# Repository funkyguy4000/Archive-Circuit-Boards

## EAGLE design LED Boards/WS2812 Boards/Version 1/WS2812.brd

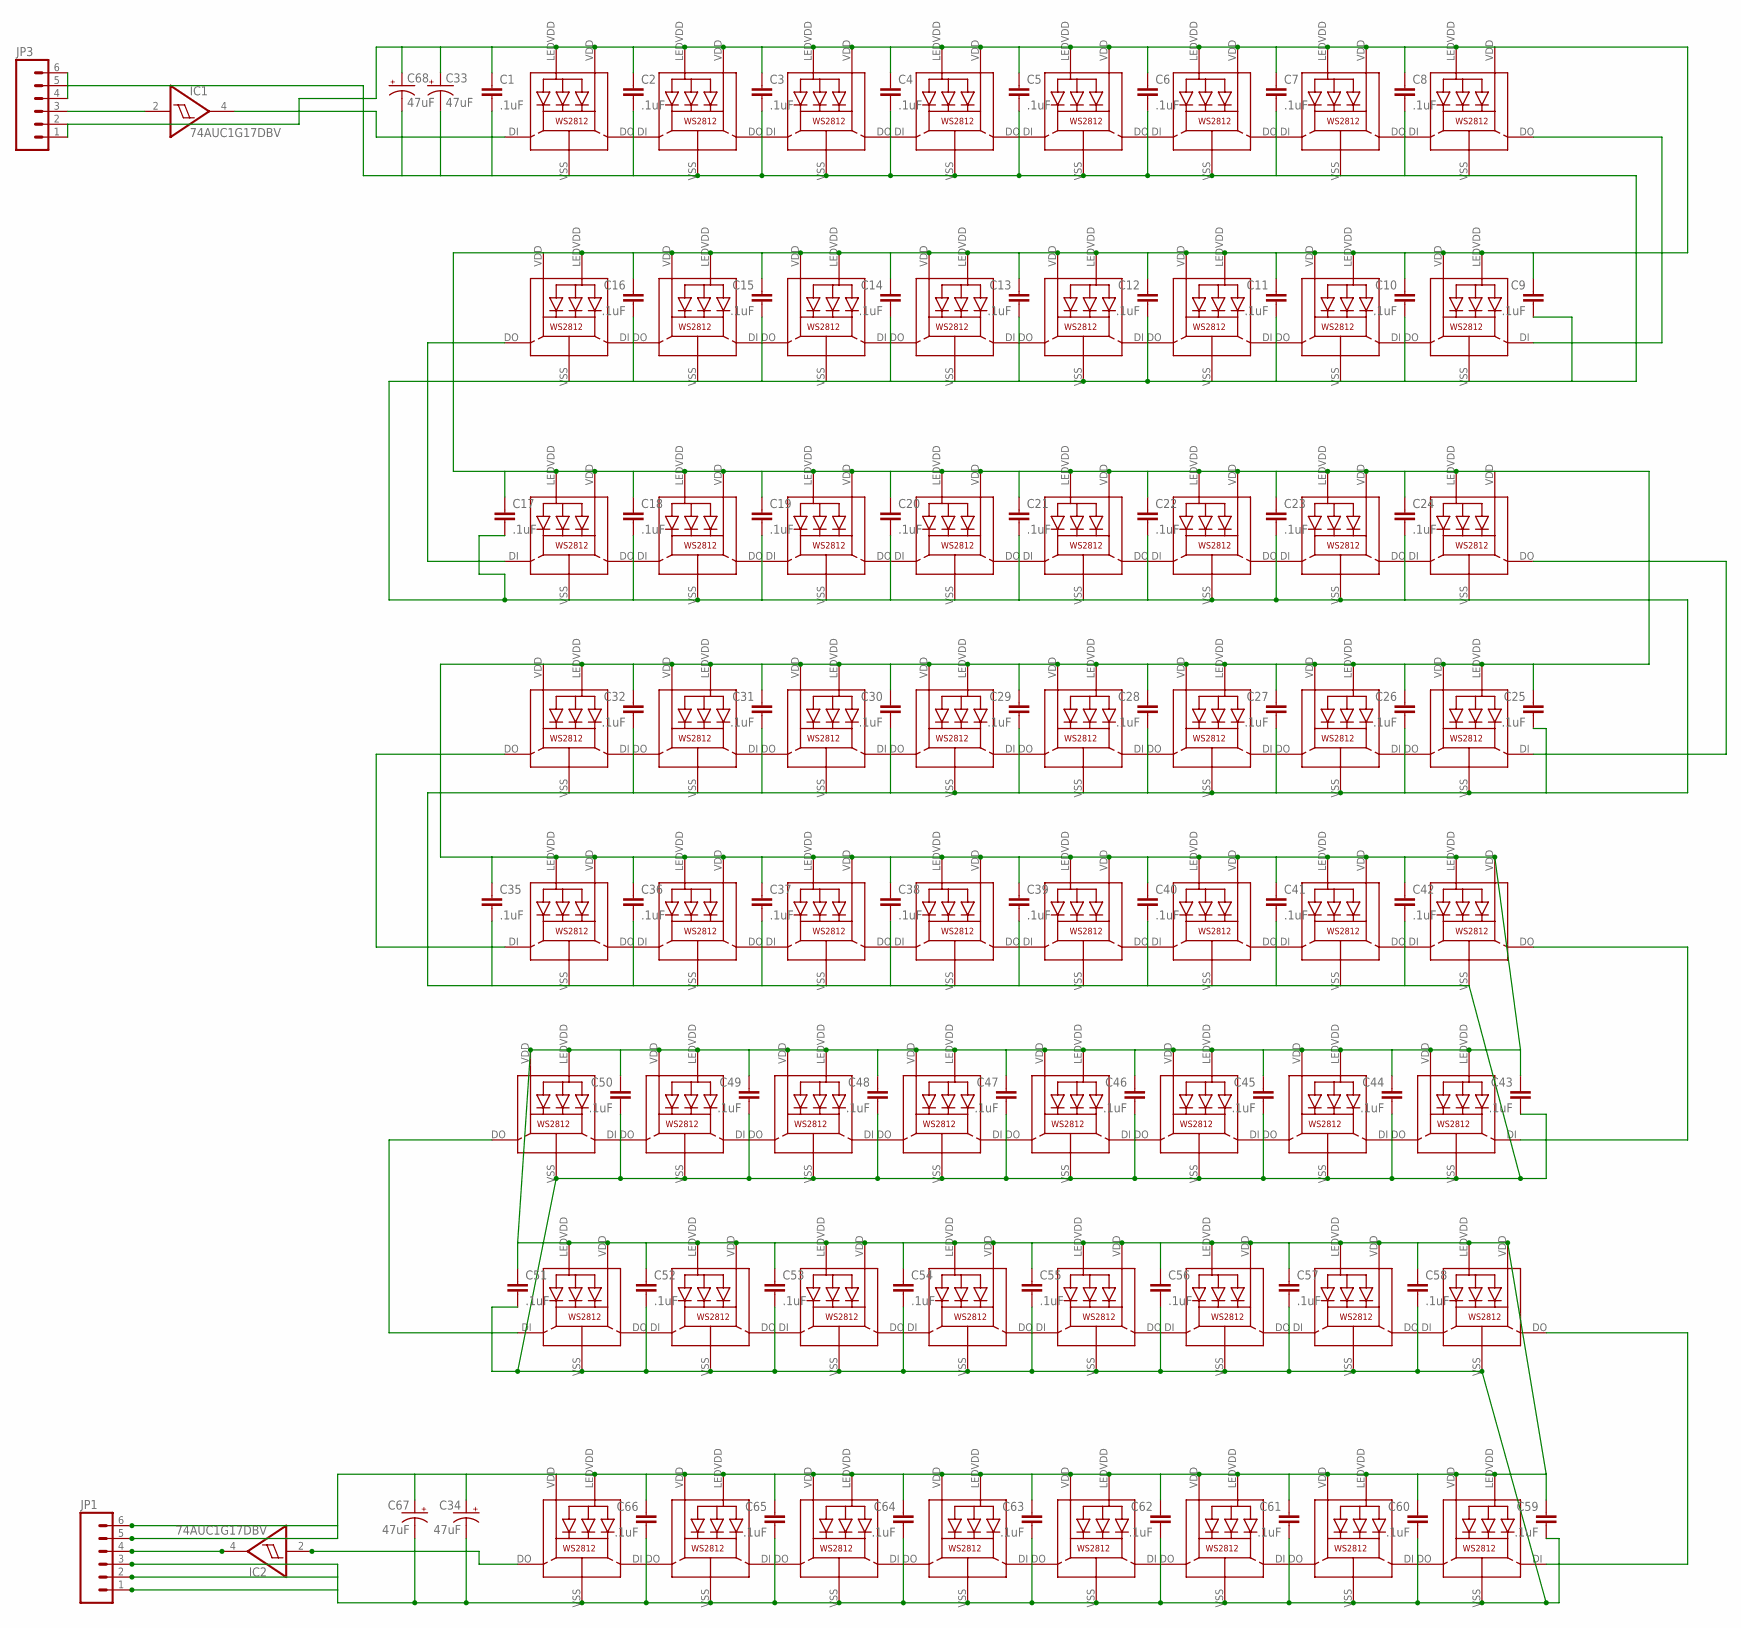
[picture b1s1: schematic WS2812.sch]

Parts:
C1, C2, C3, C4, C5, C6, C7, C8, C9, C10, C11, C12, C13, C14, C15, C16, C17, C18, C19, C20, C21, C22, C23, C24, C25, C26, C27, C28, C29, C30, C31, C32, C35, C36, C37, C38, C39, C40, C41, C42, C43, C44, C45, C46, C47, C48, C49, C50, C51, C52, C53, C54, C55, C56, C57, C58, C59, C60, C61, C62, C63, C64, C65, C66: .1uF; 0603-CAP
C33, C34, C67, C68: 47uF; EIA3216
IC1, IC2: 74AUC1G17DBV; SOT23-5
JP1, JP3: M06SMD; 1X06-SMD
LED1, LED2, LED3, LED4, LED5, LED6, LED7, LED8, LED9, LED10, LED11, LED12, LED13, LED14, LED15, LED16, LED17, LED18, LED19, LED20, LED21, LED22, LED23, LED24, LED25, LED26, LED27, LED28, LED29, LED30, LED31, LED32, LED33, LED34, LED35, LED36, LED37, LED38, LED39, LED40, LED41, LED42, LED43, LED44, LED45, LED46, LED47, LED48, LED49, LED50, LED51, LED52, LED53, LED54, LED55, LED56, LED57, LED58, LED59, LED60, LED61, LED62, LED63, LED64: WS2812

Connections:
DIN: IC1.4 (O), LED1.DI
DIN1: LED32.DO, LED33.DI
DIN_B: IC1.2 (I), JP3.3
DO: IC2.4 (O), JP1.4
DO_B: IC2.2 (I), LED64.DO
GND: C1.2, C2.2, C3.2, C4.2, C5.2, C6.2, C7.2, C8.2, C9.2, C10.2, C11.2, C12.2, C13.2, C14.2, C15.2, C16.2, C17.2, C18.2, C19.2, C20.2, C21.2, C22.2, C23.2, C24.2, C25.2, C26.2, C27.2, C28.2, C29.2, C30.2, C31.2, C32.2, C33.C (-), C34.C (-), C35.2, C36.2, C37.2, C38.2, C39.2, C40.2, C41.2, C42.2, C43.2, C44.2, C45.2, C46.2, C47.2, C48.2, C49.2, C50.2, C51.2, C52.2, C53.2, C54.2, C55.2, C56.2, C57.2, C58.2, C59.2, C60.2, C61.2, C62.2, C63.2, C64.2, C65.2, C66.2, C67.C (-), C68.C (-), IC1.3 (GND), IC2.3 (GND), JP1.1, JP1.2, JP1.3, JP3.4, JP3.5, JP3.6, LED1.VSS (GND), LED2.VSS (GND), LED3.VSS (GND), LED4.VSS (GND), LED5.VSS (GND), LED6.VSS (GND), LED7.VSS (GND), LED8.VSS (GND), LED9.VSS (GND), LED10.VSS (GND), LED11.VSS (GND), LED12.VSS (GND), LED13.VSS (GND), LED14.VSS (GND), LED15.VSS (GND), LED16.VSS (GND), LED17.VSS (GND), LED18.VSS (GND), LED19.VSS (GND), LED20.VSS (GND), LED21.VSS (GND), LED22.VSS (GND), LED23.VSS (GND), LED24.VSS (GND), LED25.VSS (GND), LED26.VSS (GND), LED27.VSS (GND), LED28.VSS (GND), LED29.VSS (GND), LED30.VSS (GND), LED31.VSS (GND), LED32.VSS (GND), LED33.VSS (GND), LED34.VSS (GND), LED35.VSS (GND), LED36.VSS (GND), LED37.VSS (GND), LED38.VSS (GND), LED39.VSS (GND), LED40.VSS (GND), LED41.VSS (GND), LED42.VSS (GND), LED43.VSS (GND), LED44.VSS (GND), LED45.VSS (GND), LED46.VSS (GND), LED47.VSS (GND), LED48.VSS (GND), LED49.VSS (GND), LED50.VSS (GND), LED51.VSS (GND), LED52.VSS (GND), LED53.VSS (GND), LED54.VSS (GND), LED55.VSS (GND), LED56.VSS (GND), LED57.VSS (GND), LED58.VSS (GND), LED59.VSS (GND), LED60.VSS (GND), LED61.VSS (GND), LED62.VSS (GND), LED63.VSS (GND), LED64.VSS (GND)
unnamed: LED1.DO, LED2.DI
unnamed: LED2.DO, LED3.DI
unnamed: LED3.DO, LED4.DI
unnamed: LED5.DO, LED6.DI
unnamed: LED6.DO, LED7.DI
unnamed: LED7.DO, LED8.DI
unnamed: LED9.DO, LED10.DI
unnamed: LED10.DO, LED11.DI
unnamed: LED11.DO, LED12.DI
unnamed: LED13.DO, LED14.DI
unnamed: LED14.DO, LED15.DI
unnamed: LED15.DO, LED16.DI
unnamed: LED17.DO, LED18.DI
unnamed: LED18.DO, LED19.DI
unnamed: LED19.DO, LED20.DI
unnamed: LED21.DO, LED22.DI
unnamed: LED22.DO, LED23.DI
unnamed: LED23.DO, LED24.DI
unnamed: LED25.DO, LED26.DI
unnamed: LED26.DO, LED27.DI
unnamed: LED27.DO, LED28.DI
unnamed: LED29.DO, LED30.DI
unnamed: LED30.DO, LED31.DI
unnamed: LED31.DO, LED32.DI
unnamed: LED4.DO, LED5.DI
unnamed: LED16.DO, LED17.DI
unnamed: LED33.DO, LED34.DI
unnamed: LED34.DO, LED35.DI
unnamed: LED35.DO, LED36.DI
unnamed: LED37.DO, LED38.DI
unnamed: LED38.DO, LED39.DI
unnamed: LED39.DO, LED40.DI
unnamed: LED41.DO, LED42.DI
unnamed: LED42.DO, LED43.DI
unnamed: LED43.DO, LED44.DI
unnamed: LED45.DO, LED46.DI
unnamed: LED46.DO, LED47.DI
unnamed: LED47.DO, LED48.DI
unnamed: LED49.DO, LED50.DI
unnamed: LED50.DO, LED51.DI
unnamed: LED51.DO, LED52.DI
unnamed: LED53.DO, LED54.DI
unnamed: LED54.DO, LED55.DI
unnamed: LED55.DO, LED56.DI
unnamed: LED57.DO, LED58.DI
unnamed: LED58.DO, LED59.DI
unnamed: LED59.DO, LED60.DI
unnamed: LED61.DO, LED62.DI
unnamed: LED62.DO, LED63.DI
unnamed: LED63.DO, LED64.DI
unnamed: LED12.DO, LED13.DI
unnamed: LED20.DO, LED21.DI
unnamed: LED44.DO, LED45.DI
unnamed: LED52.DO, LED53.DI
unnamed: LED28.DO, LED29.DI
unnamed: LED8.DO, LED9.DI
unnamed: LED40.DO, LED41.DI
unnamed: LED24.DO, LED25.DI
unnamed: LED36.DO, LED37.DI
unnamed: LED60.DO, LED61.DI
unnamed: LED48.DO, LED49.DI
unnamed: LED56.DO, LED57.DI
VDD: C1.1, C2.1, C3.1, C4.1, C5.1, C6.1, C7.1, C8.1, C9.1, C10.1, C11.1, C12.1, C13.1, C14.1, C15.1, C16.1, C17.1, C18.1, C19.1, C20.1, C21.1, C22.1, C23.1, C24.1, C25.1, C26.1, C27.1, C28.1, C29.1, C30.1, C31.1, C32.1, C33.A (+), C34.A (+), C35.1, C36.1, C37.1, C38.1, C39.1, C40.1, C41.1, C42.1, C43.1, C44.1, C45.1, C46.1, C47.1, C48.1, C49.1, C50.1, C51.1, C52.1, C53.1, C54.1, C55.1, C56.1, C57.1, C58.1, C59.1, C60.1, C61.1, C62.1, C63.1, C64.1, C65.1, C66.1, C67.A (+), C68.A (+), IC1.5 (VCC), IC2.5 (VCC), JP1.5, JP1.6, JP3.1, JP3.2, LED1.LEDVDD, LED1.VDD, LED2.LEDVDD, LED2.VDD, LED3.LEDVDD, LED3.VDD, LED4.LEDVDD, LED4.VDD, LED5.LEDVDD, LED5.VDD, LED6.LEDVDD, LED6.VDD, LED7.LEDVDD, LED7.VDD, LED8.LEDVDD, LED8.VDD, LED9.LEDVDD, LED9.VDD, LED10.LEDVDD, LED10.VDD, LED11.LEDVDD, LED11.VDD, LED12.LEDVDD, LED12.VDD, LED13.LEDVDD, LED13.VDD, LED14.LEDVDD, LED14.VDD, LED15.LEDVDD, LED15.VDD, LED16.LEDVDD, LED16.VDD, LED17.LEDVDD, LED17.VDD, LED18.LEDVDD, LED18.VDD, LED19.LEDVDD, LED19.VDD, LED20.LEDVDD, LED20.VDD, LED21.LEDVDD, LED21.VDD, LED22.LEDVDD, LED22.VDD, LED23.LEDVDD, LED23.VDD, LED24.LEDVDD, LED24.VDD, LED25.LEDVDD, LED25.VDD, LED26.LEDVDD, LED26.VDD, LED27.LEDVDD, LED27.VDD, LED28.LEDVDD, LED28.VDD, LED29.LEDVDD, LED29.VDD, LED30.LEDVDD, LED30.VDD, LED31.LEDVDD, LED31.VDD, LED32.LEDVDD, LED32.VDD, LED33.LEDVDD, LED33.VDD, LED34.LEDVDD, LED34.VDD, LED35.LEDVDD, LED35.VDD, LED36.LEDVDD, LED36.VDD, LED37.LEDVDD, LED37.VDD, LED38.LEDVDD, LED38.VDD, LED39.LEDVDD, LED39.VDD, LED40.LEDVDD, LED40.VDD, LED41.LEDVDD, LED41.VDD, LED42.LEDVDD, LED42.VDD, LED43.LEDVDD, LED43.VDD, LED44.LEDVDD, LED44.VDD, LED45.LEDVDD, LED45.VDD, LED46.LEDVDD, LED46.VDD, LED47.LEDVDD, LED47.VDD, LED48.LEDVDD, LED48.VDD, LED49.LEDVDD, LED49.VDD, LED50.LEDVDD, LED50.VDD, LED51.LEDVDD, LED51.VDD, LED52.LEDVDD, LED52.VDD, LED53.LEDVDD, LED53.VDD, LED54.LEDVDD, LED54.VDD, LED55.LEDVDD, LED55.VDD, LED56.LEDVDD, LED56.VDD, LED57.LEDVDD, LED57.VDD, LED58.LEDVDD, LED58.VDD, LED59.LEDVDD, LED59.VDD, LED60.LEDVDD, LED60.VDD, LED61.LEDVDD, LED61.VDD, LED62.LEDVDD, LED62.VDD, LED63.LEDVDD, LED63.VDD, LED64.LEDVDD, LED64.VDD

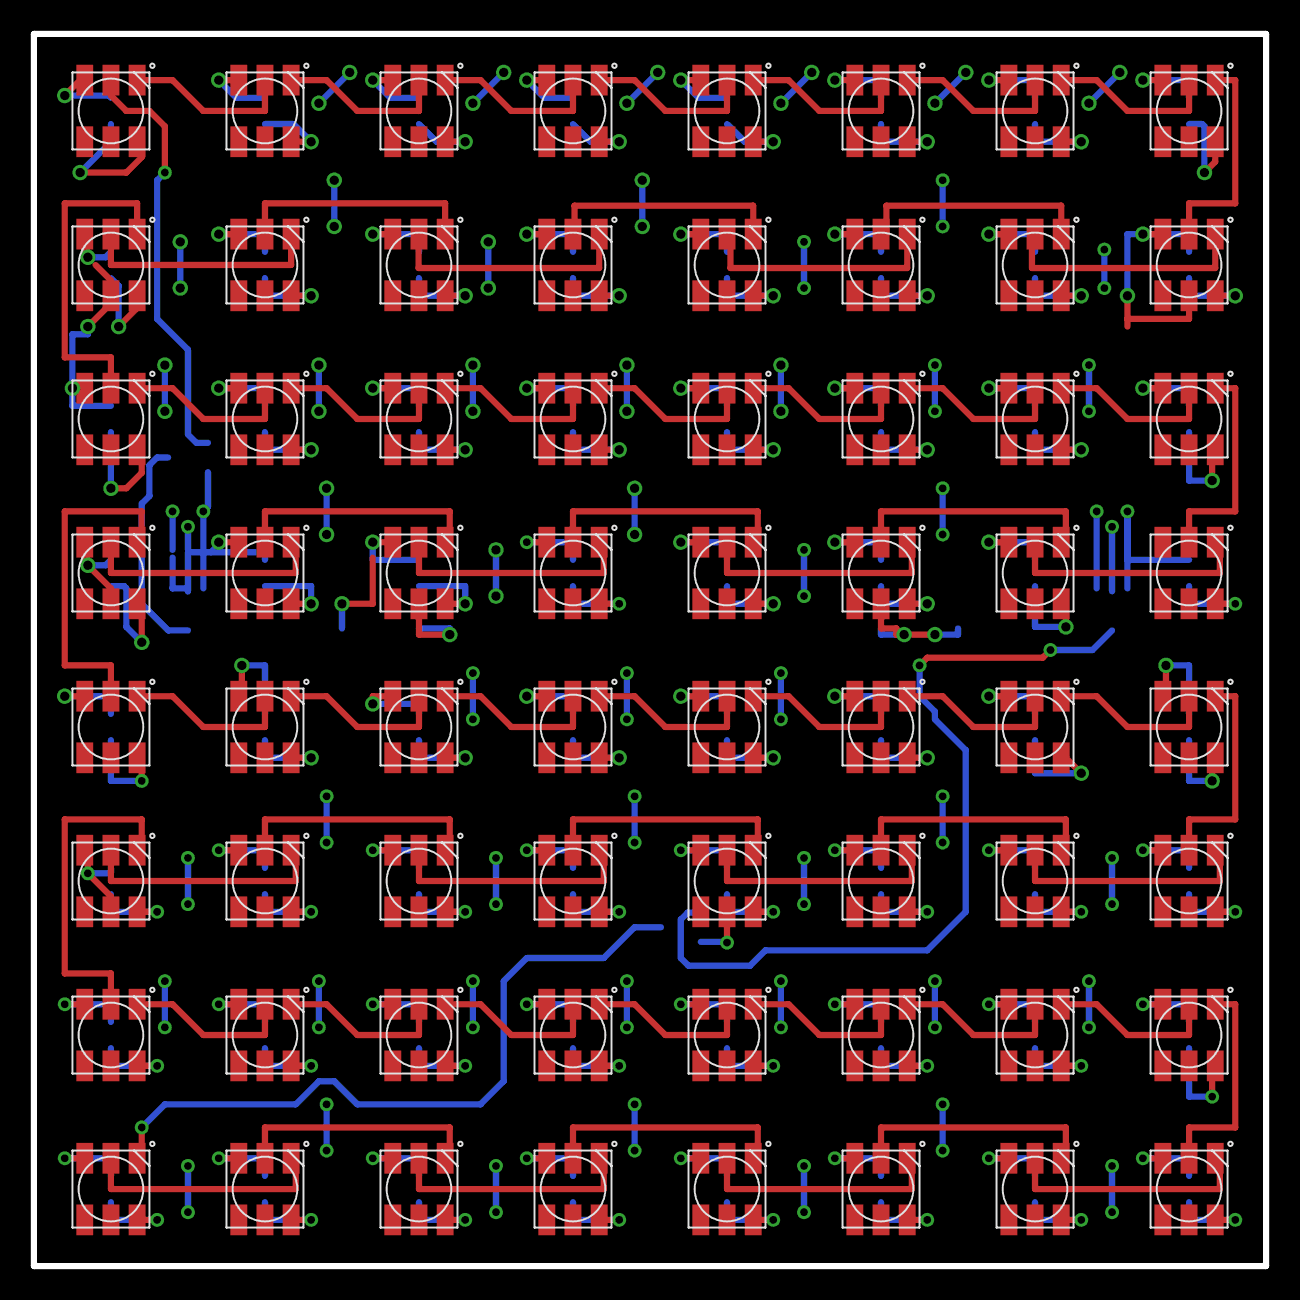
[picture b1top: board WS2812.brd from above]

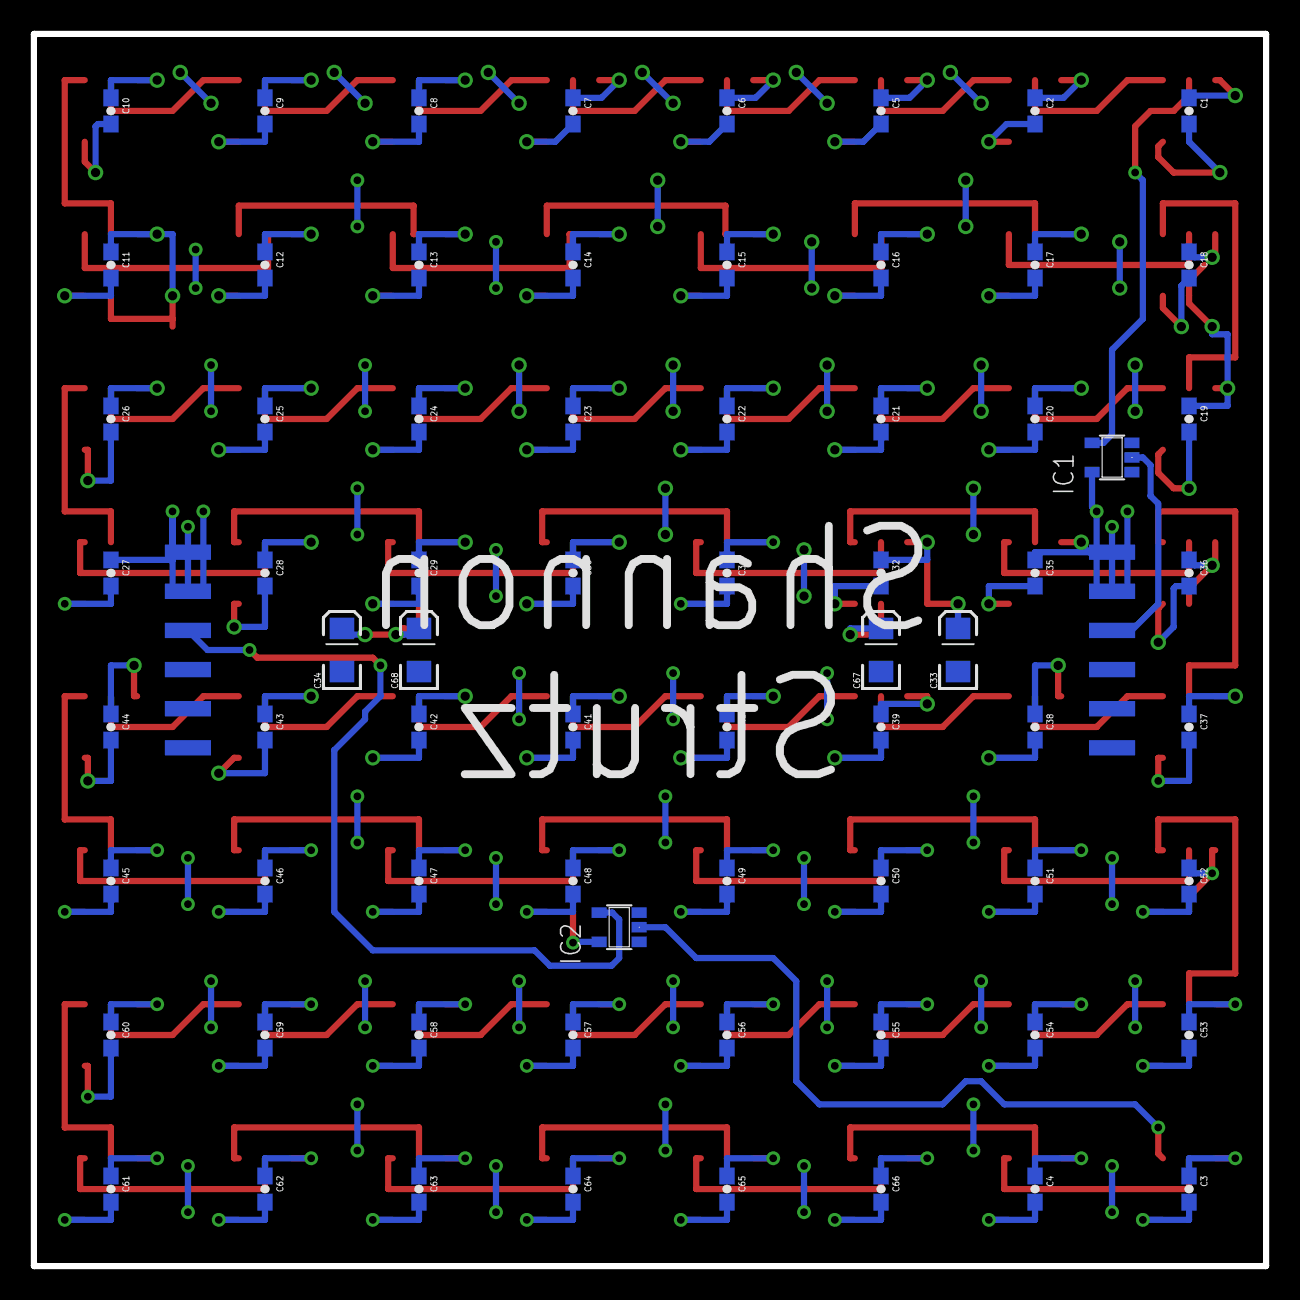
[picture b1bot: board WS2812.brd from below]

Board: 2 copper layers, 80.0 x 80.0 mm, 136 parts (72 on the bottom side), 69 nets.

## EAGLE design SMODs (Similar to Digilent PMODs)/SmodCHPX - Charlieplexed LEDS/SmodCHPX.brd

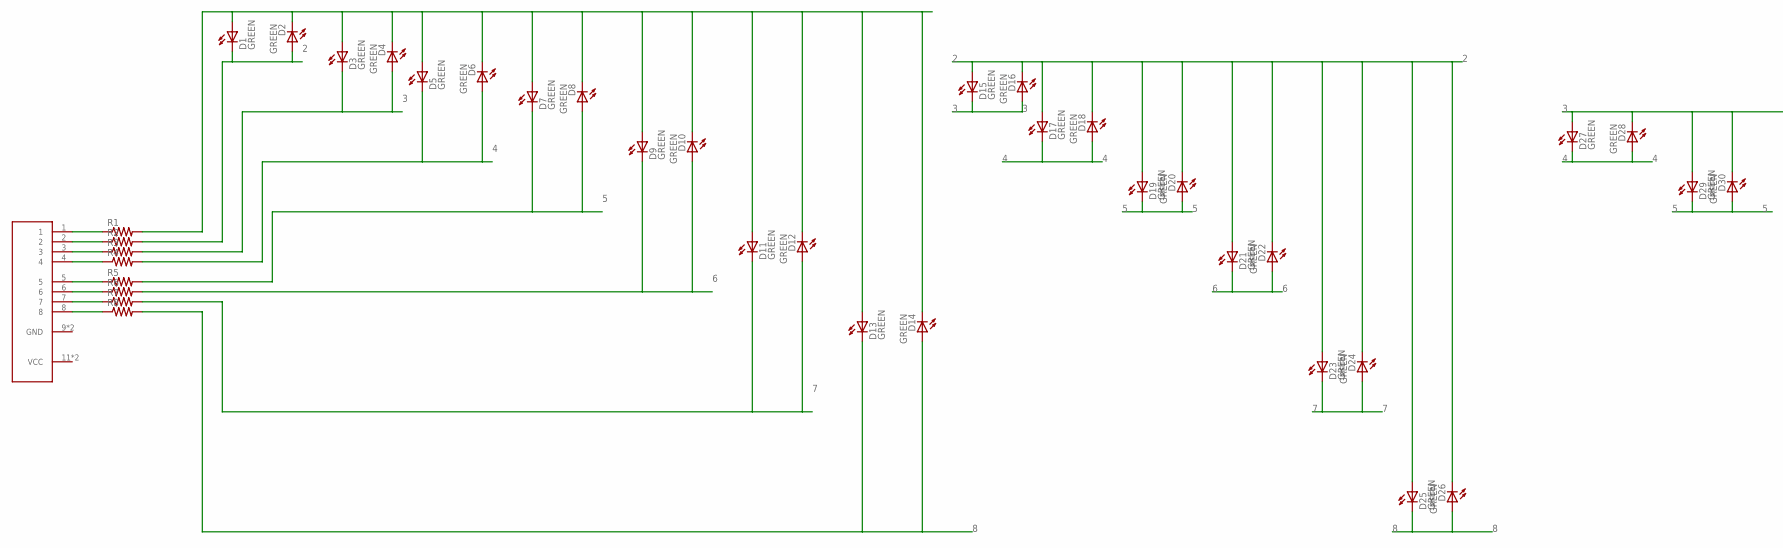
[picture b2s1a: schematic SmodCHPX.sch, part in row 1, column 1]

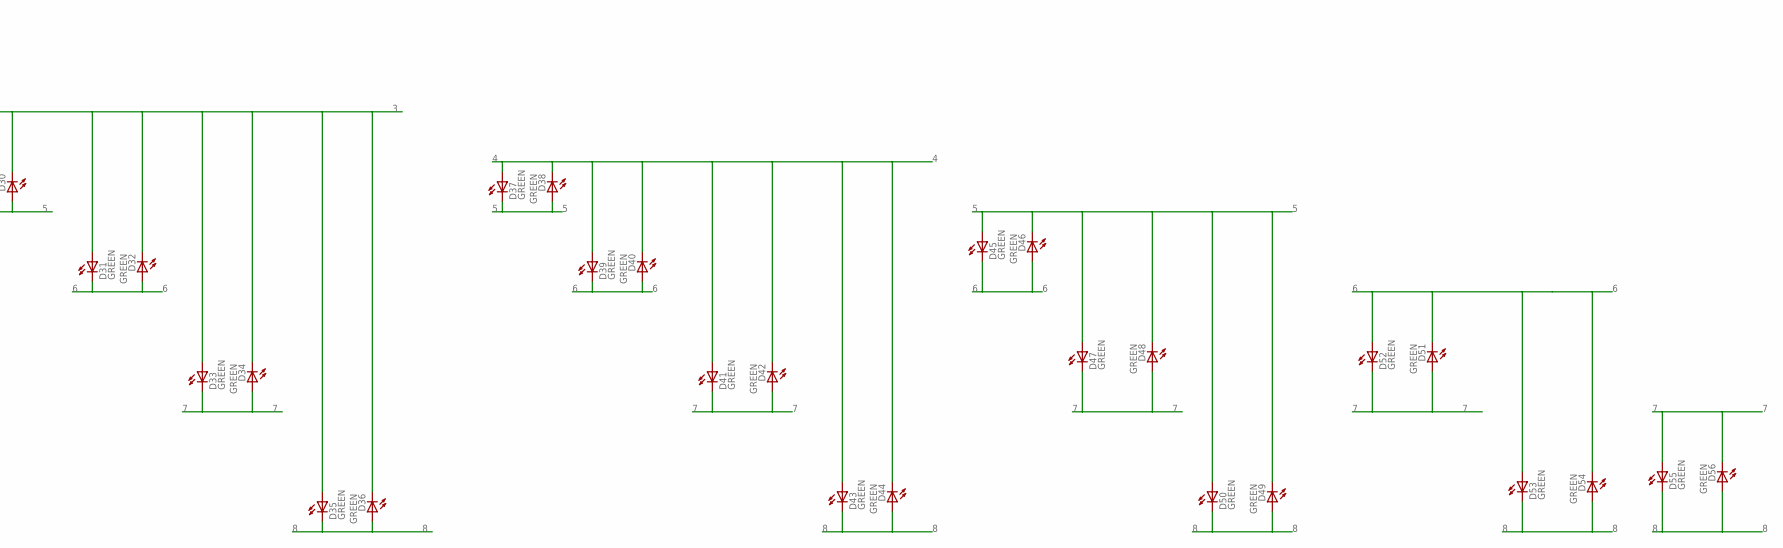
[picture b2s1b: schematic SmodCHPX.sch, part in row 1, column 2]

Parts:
D1, D2, D3, D4, D5, D6, D7, D8, D9, D10, D11, D12, D13, D14, D15, D16, D17, D18, D19, D20, D21, D22, D23, D24, D25, D26, D27, D28, D29, D30, D31, D32, D33, D34, D35, D36, D37, D38, D39, D40, D41, D42, D43, D44, D45, D46, D47, D48, D49, D50, D51, D52, D53, D54, D55, D56: GREEN; LED-1206
R1, R2, R3, R4, R5, R6, R7, R8: RESISTOR1206; 1206
U$1: PMOD; 2X6

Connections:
1: D1.A, D2.C, D3.A, D4.C, D5.A, D6.C, D7.A, D8.C, D9.A, D10.C, D11.A, D12.C, D13.A, D14.C, R1.2
2: D1.C, D2.A, D15.A, D16.C, D17.A, D18.C, D19.A, D20.C, D21.A, D22.C, D23.A, D24.C, D25.A, D26.C, R2.2
3: D3.C, D4.A, D15.C, D16.A, D27.A, D28.C, D29.A, D30.C, D31.A, D32.C, D33.A, D34.C, D35.A, D36.C, R3.2
4: D5.C, D6.A, D17.C, D18.A, D27.C, D28.A, D37.A, D38.C, D39.A, D40.C, D41.A, D42.C, D43.A, D44.C, R4.2
5: D7.C, D8.A, D19.C, D20.A, D29.C, D30.A, D37.C, D38.A, D45.A, D46.C, D47.A, D48.C, D49.C, D50.A, R5.2
6: D9.C, D10.A, D21.C, D22.A, D31.C, D32.A, D39.C, D40.A, D45.C, D46.A, D51.C, D52.A, D53.A, D54.C, R6.2
7: D11.C, D12.A, D23.C, D24.A, D33.C, D34.A, D41.C, D42.A, D47.C, D48.A, D51.A, D52.C, D55.A, D56.C, R7.2
8: D13.C, D14.A, D25.C, D26.A, D35.C, D36.A, D43.C, D44.A, D49.A, D50.C, D53.C, D54.A, D55.C, D56.A, R8.2
unnamed: R1.1, U$1.1
unnamed: R2.1, U$1.2
unnamed: R3.1, U$1.3
unnamed: R4.1, U$1.4
unnamed: R5.1, U$1.5
unnamed: R6.1, U$1.6
unnamed: R7.1, U$1.7
unnamed: R8.1, U$1.8

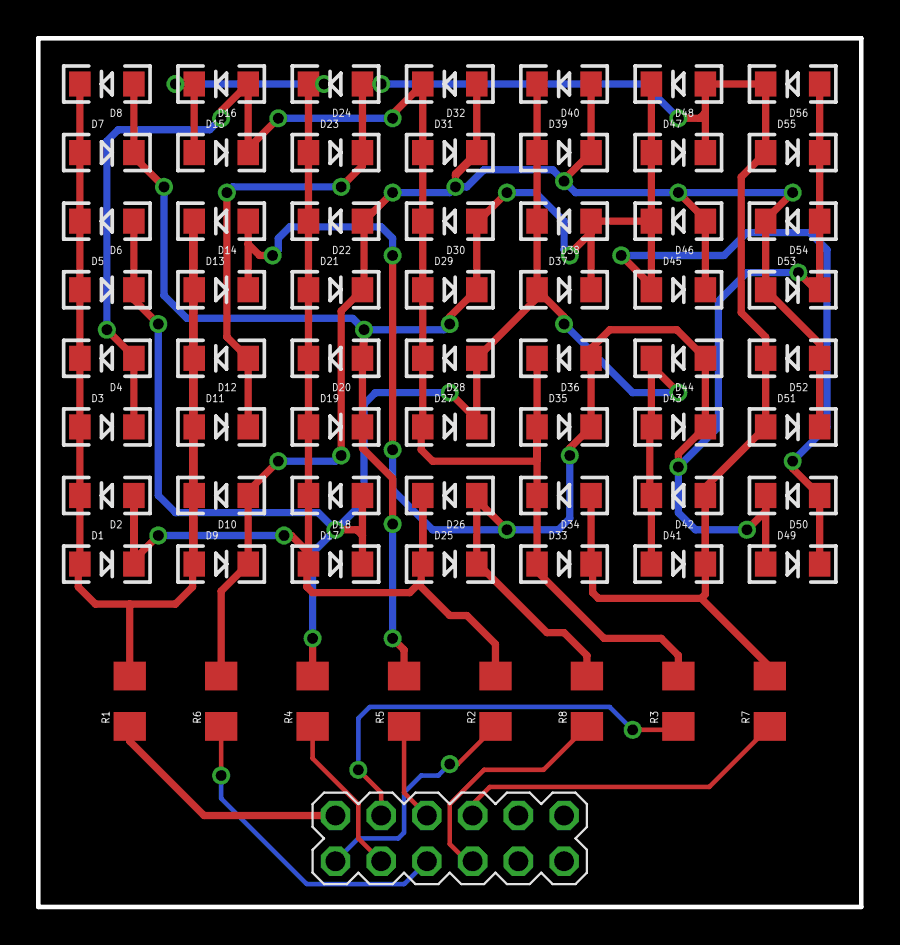
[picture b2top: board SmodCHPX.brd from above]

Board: 2 copper layers, 45.7 x 48.3 mm, 65 parts (0 on the bottom side), 16 nets.

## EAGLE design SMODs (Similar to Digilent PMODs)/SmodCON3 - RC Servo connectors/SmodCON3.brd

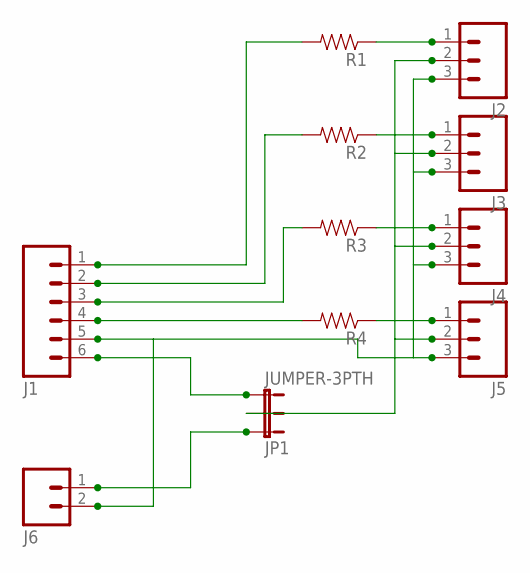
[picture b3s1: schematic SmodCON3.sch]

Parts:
J1: M06SIP; 1X06
J2, J3, J4, J5: M03PTH; 1X03
J6: M023.5MM; SCREWTERMINAL-3.5MM-2
JP1: JUMPER-3PTH; 1X03
R1, R2, R3, R4: RESISTOR0603-RES; 0603-RES

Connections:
GND: J1.5, J2.3, J3.3, J4.3, J5.3, J6.2
unnamed: J2.1, R1.1
unnamed: J3.1, R2.1
unnamed: J4.1, R3.1
unnamed: J5.1, R4.1
P1: J1.1, R1.2
P2: J1.2, R2.2
P3: J1.3, R3.2
P4: J1.4, R4.2
VCC: J1.6, JP1.3
VE: J6.1, JP1.1
VS: J2.2, J3.2, J4.2, J5.2, JP1.2

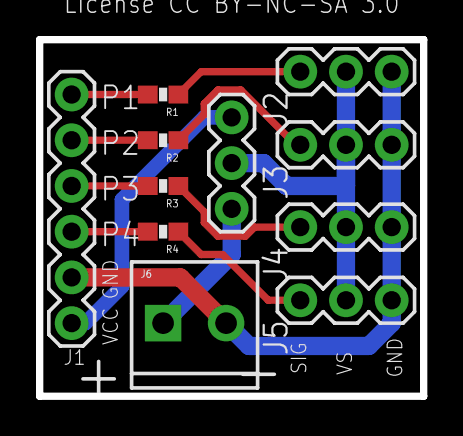
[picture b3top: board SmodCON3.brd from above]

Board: 2 copper layers, 21.3 x 19.8 mm, 11 parts (0 on the bottom side), 12 nets.

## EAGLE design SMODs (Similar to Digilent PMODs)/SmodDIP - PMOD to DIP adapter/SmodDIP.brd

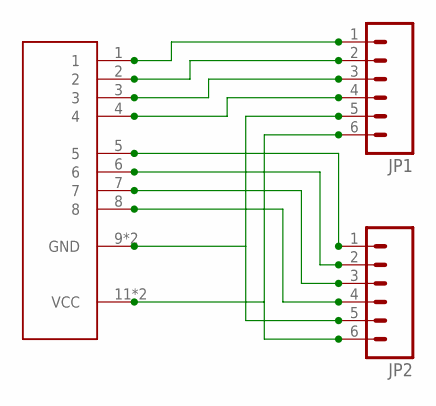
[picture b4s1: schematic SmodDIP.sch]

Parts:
JP1, JP2: M06LOCK; 1X06_LOCK
U$1: PMOD; 2X6

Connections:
GND: JP1.5, JP2.5, U$1.9 (GND), U$1.10 (GND)
unnamed: JP1.1, U$1.1
unnamed: JP1.2, U$1.2
unnamed: JP1.3, U$1.3
unnamed: JP1.4, U$1.4
unnamed: JP2.1, U$1.5
unnamed: JP2.2, U$1.6
unnamed: JP2.3, U$1.7
unnamed: JP2.4, U$1.8
VCC: JP1.6, JP2.6, U$1.11 (VCC), U$1.12 (VCC)

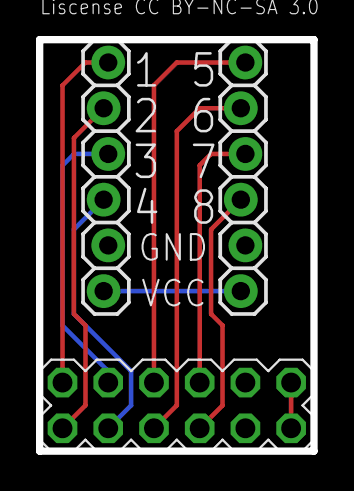
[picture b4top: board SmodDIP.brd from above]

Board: 2 copper layers, 15.2 x 22.9 mm, 3 parts (0 on the bottom side), 10 nets.

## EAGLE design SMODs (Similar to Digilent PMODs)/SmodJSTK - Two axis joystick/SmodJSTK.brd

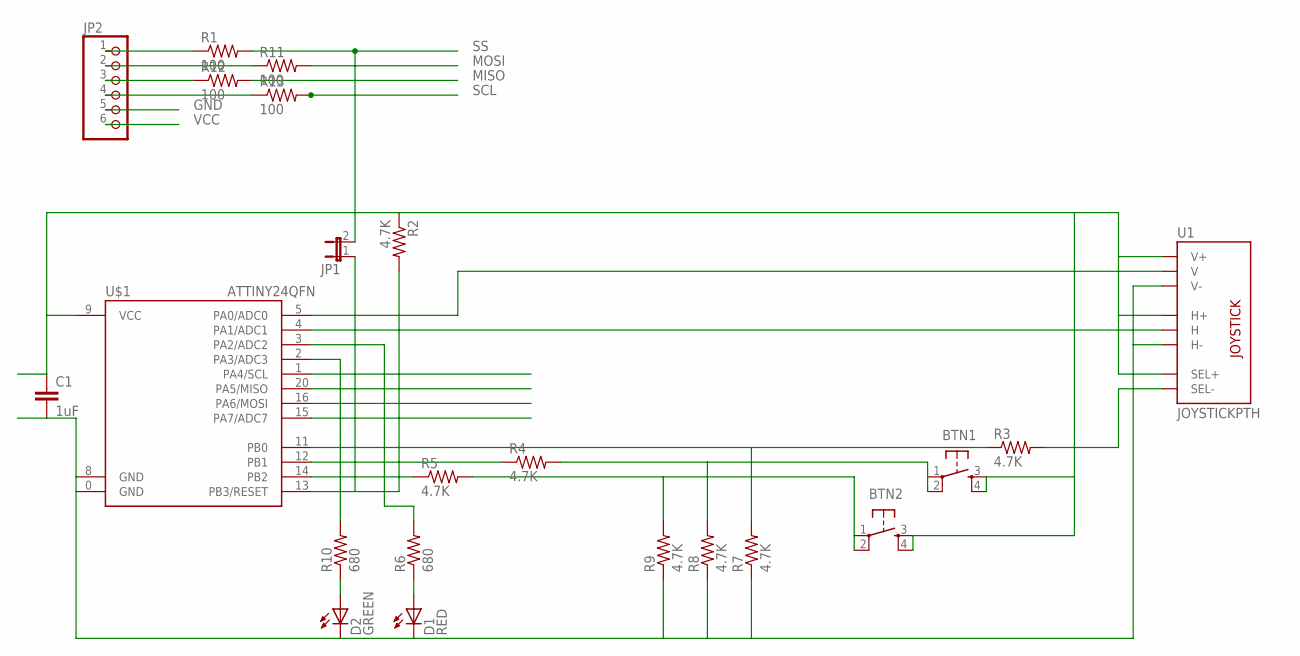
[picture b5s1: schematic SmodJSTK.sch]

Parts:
BTN1, BTN2: TAC_SWITCHPTH; TACTILE-PTH
C1: 1uF; 0603-CAP
D1: RED; LED-0603
D2: GREEN; LED-0603
JP1: JUMPER-2PTH; 1X02
JP2: PINHD-1X6; 1X06
R1, R11, R12, R13: 100; 0603-RES
R2, R3, R4, R5, R7, R8, R9: 4.7K; 0603-RES
R6, R10: 680; 0603-RES
U1: JOYSTICKPTH; JOYSTICK
U$1: ATTINY24QFN; QFN20

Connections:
GND: C1.2, D1.C, D2.C, JP2.5, R7.1, R8.1, R9.1, U1.H3 (H-), U1.V3 (V-), U$1.0 (GND), U$1.8 (GND)
MISO: R12.2, U$1.20 (PA5/MISO)
MOSI: R11.2, U$1.16 (PA6/MOSI)
unnamed: BTN1.1, BTN1.2, R4.2, R8.2
unnamed: BTN2.1, BTN2.2, R5.2, R9.2
unnamed: JP1.1, R2.2, U$1.13 (PB3/RESET)
unnamed: R3.1, R7.2, U$1.11 (PB0)
unnamed: R3.2, U1.B2A (SEL-)
unnamed: R5.1, U$1.14 (PB2)
unnamed: JP2.1, R1.1
unnamed: R4.1, U$1.12 (PB1)
unnamed: D2.A, R10.1
unnamed: D1.A, R6.1
unnamed: R6.2, U$1.3 (PA2/ADC2)
unnamed: R10.2, U$1.2 (PA3/ADC3)
unnamed: U1.V2 (V), U$1.5 (PA0/ADC0)
unnamed: U1.H2 (H), U$1.4 (PA1/ADC1)
unnamed: JP2.2, R11.1
unnamed: JP2.3, R12.1
unnamed: JP2.4, R13.1
SCL: R13.2, U$1.1 (PA4/SCL)
SS: JP1.2, R1.2, U$1.15 (PA7/ADC7)
VCC: BTN1.3, BTN1.4, BTN2.3, BTN2.4, C1.1, JP2.6, R2.1, U1.B1A (SEL+), U1.H1 (H+), U1.V1 (V+), U$1.9 (VCC)

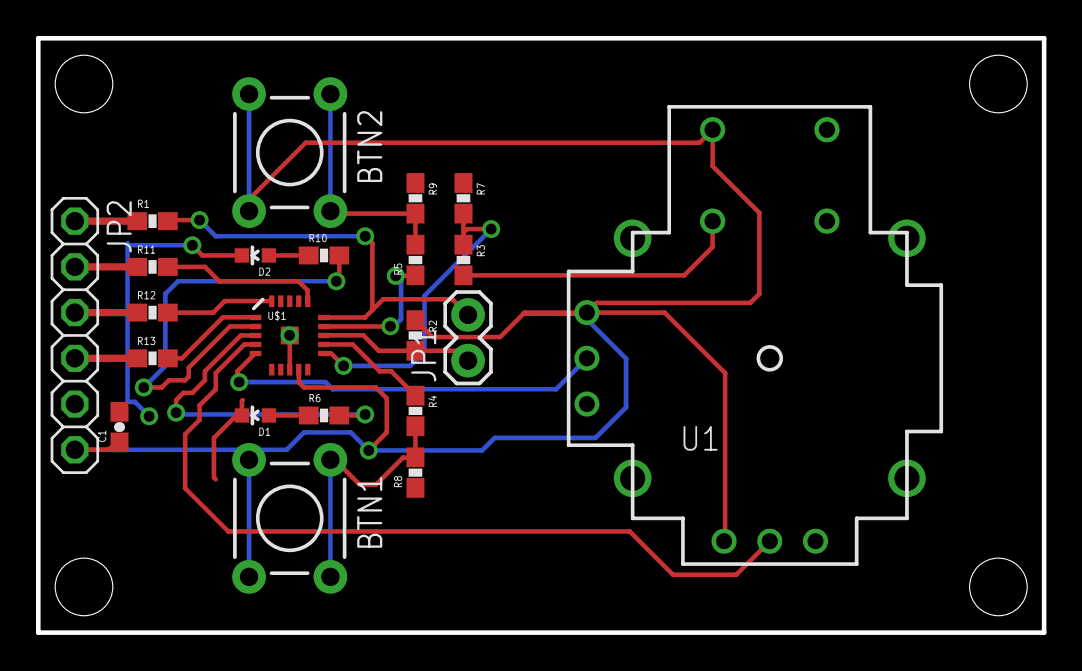
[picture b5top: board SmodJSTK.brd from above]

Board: 2 copper layers, 55.9 x 33.0 mm, 22 parts (0 on the bottom side), 23 nets.

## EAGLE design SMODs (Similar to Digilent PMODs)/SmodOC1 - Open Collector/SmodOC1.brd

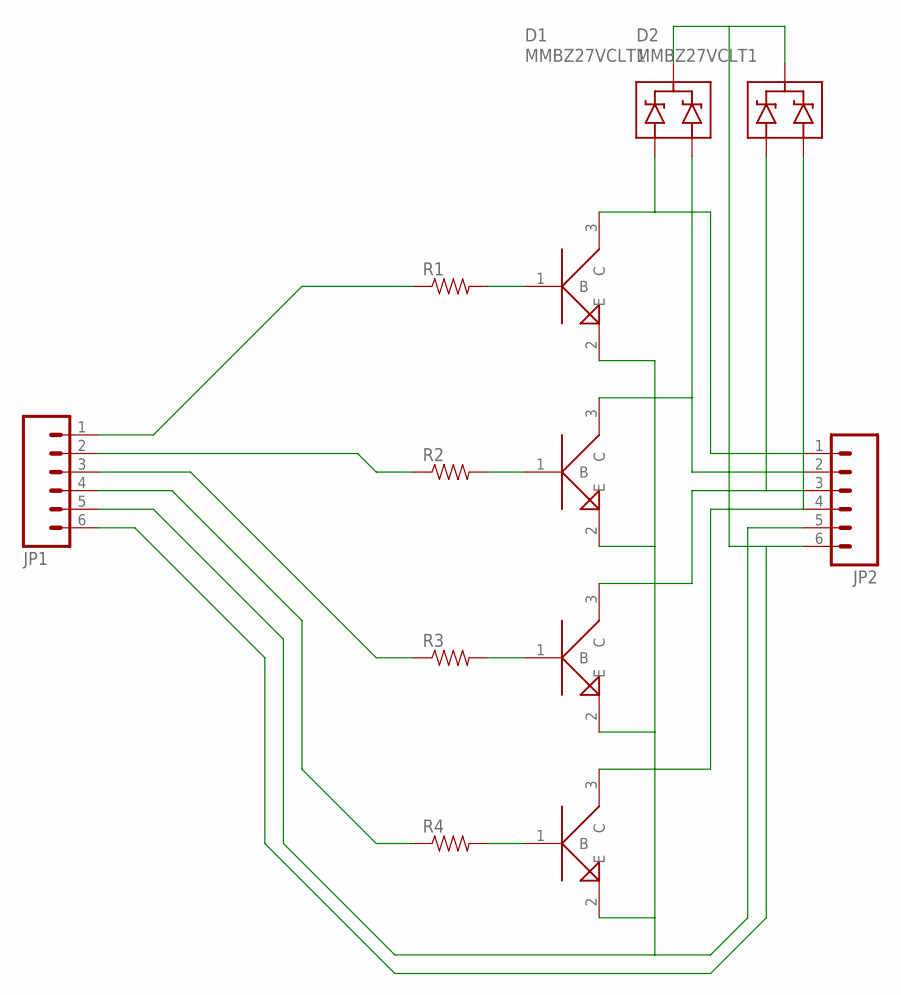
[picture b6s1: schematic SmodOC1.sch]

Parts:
D1, D2: MMBZ27VCLT1; SOT23-3
JP1, JP2: M06POGOPIN_HOLES_ONLY; 1X06_HOLES_ONLY
Q1, Q2, Q3, Q4: MMBT3904; SOT-23
R1, R2, R3, R4: RESISTOR0603-RES; 0603-RES

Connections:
GND: JP1.5, JP2.5, Q1.2 (E), Q2.2 (E), Q3.2 (E), Q4.2 (E)
unnamed: Q1.1 (B), R1.2
unnamed: Q2.1 (B), R2.2
unnamed: Q3.1 (B), R3.2
unnamed: Q4.1 (B), R4.2
Q1: JP1.1, R1.1
Q2: JP1.2, R2.1
Q3: JP1.3, R3.1
Q4: JP1.4, R4.1
QO1: D1.1 (A1), JP2.1, Q1.3 (C)
QO2: D1.2 (A2), JP2.2, Q2.3 (C)
QO3: D2.1 (A1), JP2.3, Q3.3 (C)
QO4: D2.2 (A2), JP2.4, Q4.3 (C)
VCC: D1.3 (C), D2.3 (C), JP1.6, JP2.6

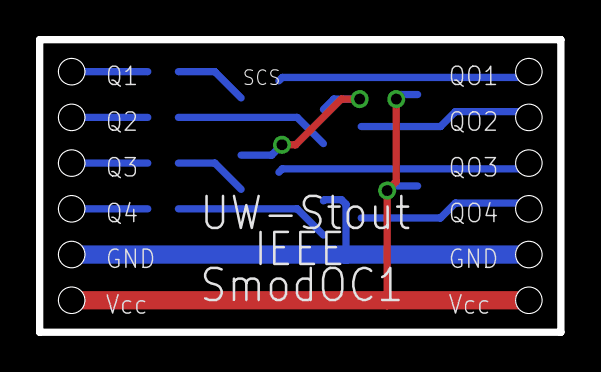
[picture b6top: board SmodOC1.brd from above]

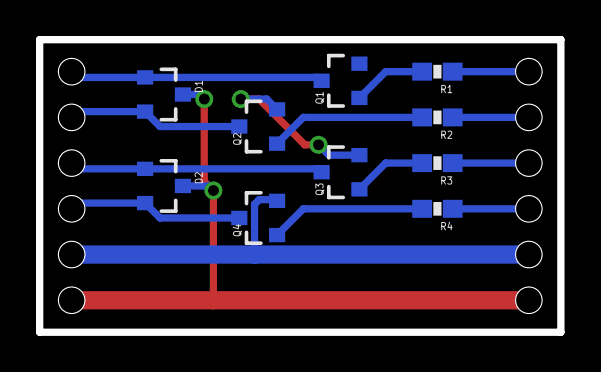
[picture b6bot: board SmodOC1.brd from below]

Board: 2 copper layers, 29.0 x 16.3 mm, 12 parts (10 on the bottom side), 14 nets.

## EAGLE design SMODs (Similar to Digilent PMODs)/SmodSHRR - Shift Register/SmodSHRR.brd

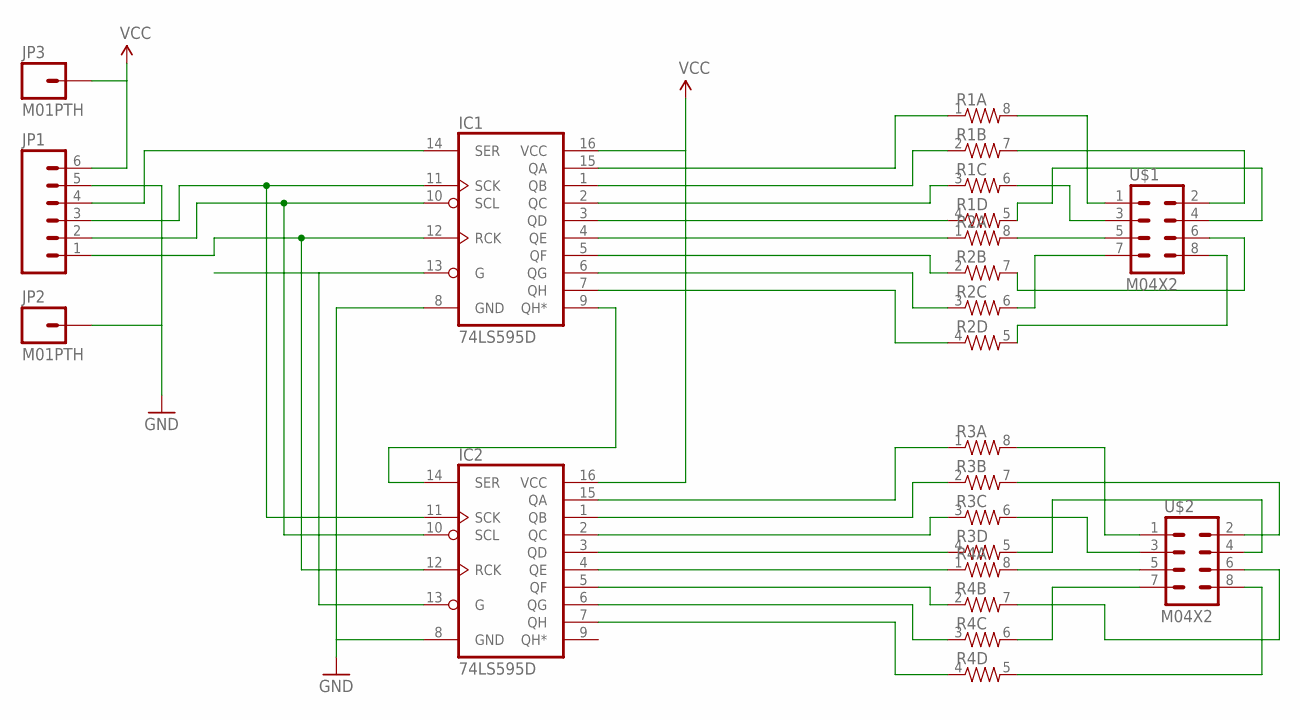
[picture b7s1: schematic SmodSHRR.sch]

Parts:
IC1, IC2: 74LS595D; SO16
JP1: M06SIP; 1X06
JP2, JP3: M01PTH; 1X01
R1, R2, R3, R4: RESISTOR-ARRAY0603-ARV; 0603-ARV
U$1, U$2: M04X2; 2X4

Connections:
GND: IC1.8 (GND), IC2.8 (GND), JP1.5, JP2.1
unnamed: IC1.9 (QH*), IC2.14 (SER)
unnamed: IC1.11 (SCK), IC2.11 (SCK), JP1.3
unnamed: IC1.10 (SCL), IC2.10 (SCL), JP1.2
unnamed: IC1.12 (RCK), IC2.12 (RCK), JP1.1
unnamed: R1.8 (2), U$1.1
unnamed: R1.7 (2), U$1.2
unnamed: IC1.13 (G), IC2.13 (G)
unnamed: IC1.15 (QA), R1.1
unnamed: IC1.1 (QB), R1.2 (1)
unnamed: IC1.2 (QC), R1.3 (1)
unnamed: IC1.3 (QD), R1.4 (1)
unnamed: IC1.4 (QE), R2.1
unnamed: IC1.5 (QF), R2.2 (1)
unnamed: IC1.6 (QG), R2.3 (1)
unnamed: IC1.7 (QH), R2.4 (1)
unnamed: IC2.15 (QA), R3.1
unnamed: IC2.1 (QB), R3.2 (1)
unnamed: IC2.2 (QC), R3.3 (1)
unnamed: IC2.3 (QD), R3.4 (1)
unnamed: IC2.4 (QE), R4.1
unnamed: IC2.5 (QF), R4.2 (1)
unnamed: IC2.6 (QG), R4.3 (1)
unnamed: IC2.7 (QH), R4.4 (1)
unnamed: R3.8 (2), U$2.1
unnamed: R1.6 (2), U$1.3
unnamed: R1.5 (2), U$1.4
unnamed: R2.8 (2), U$1.5
unnamed: R2.7 (2), U$1.6
unnamed: R2.6 (2), U$1.7
unnamed: R2.5 (2), U$1.8
unnamed: R3.7 (2), U$2.2
unnamed: R3.6 (2), U$2.3
unnamed: R3.5 (2), U$2.4
unnamed: R4.8 (2), U$2.5
unnamed: R4.7 (2), U$2.6
unnamed: R4.6 (2), U$2.7
unnamed: R4.5 (2), U$2.8
unnamed: IC1.14 (SER), JP1.4
VCC: IC1.16 (VCC), IC2.16 (VCC), JP1.6, JP3.1

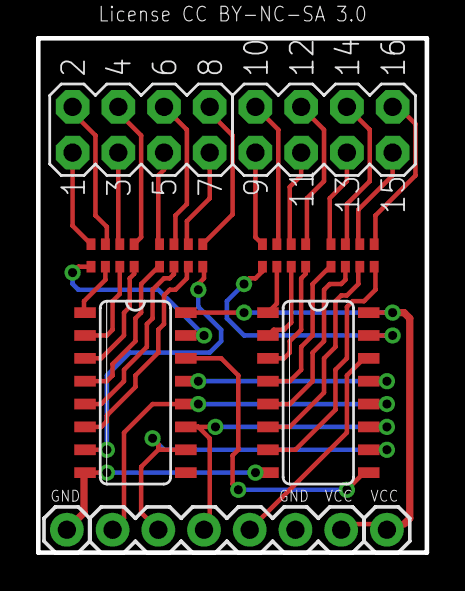
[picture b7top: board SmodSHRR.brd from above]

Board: 2 copper layers, 21.6 x 28.6 mm, 11 parts (0 on the bottom side), 40 nets.

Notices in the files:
SMODs (Similar to Digilent PMODs)/SmodCON3 - RC Servo connectors/SmodCON3.brd:
License CC BY-NC-SA 3.0
SMODs (Similar to Digilent PMODs)/SmodDIP - PMOD to DIP adapter/SmodDIP.brd:
Liscense CC BY-NC-SA 3.0
parts and their libraries:
SparkFun-Capacitors: Licensing: CC v3.0 Share-Alike You are welcome to use this library for commercial purposes.
